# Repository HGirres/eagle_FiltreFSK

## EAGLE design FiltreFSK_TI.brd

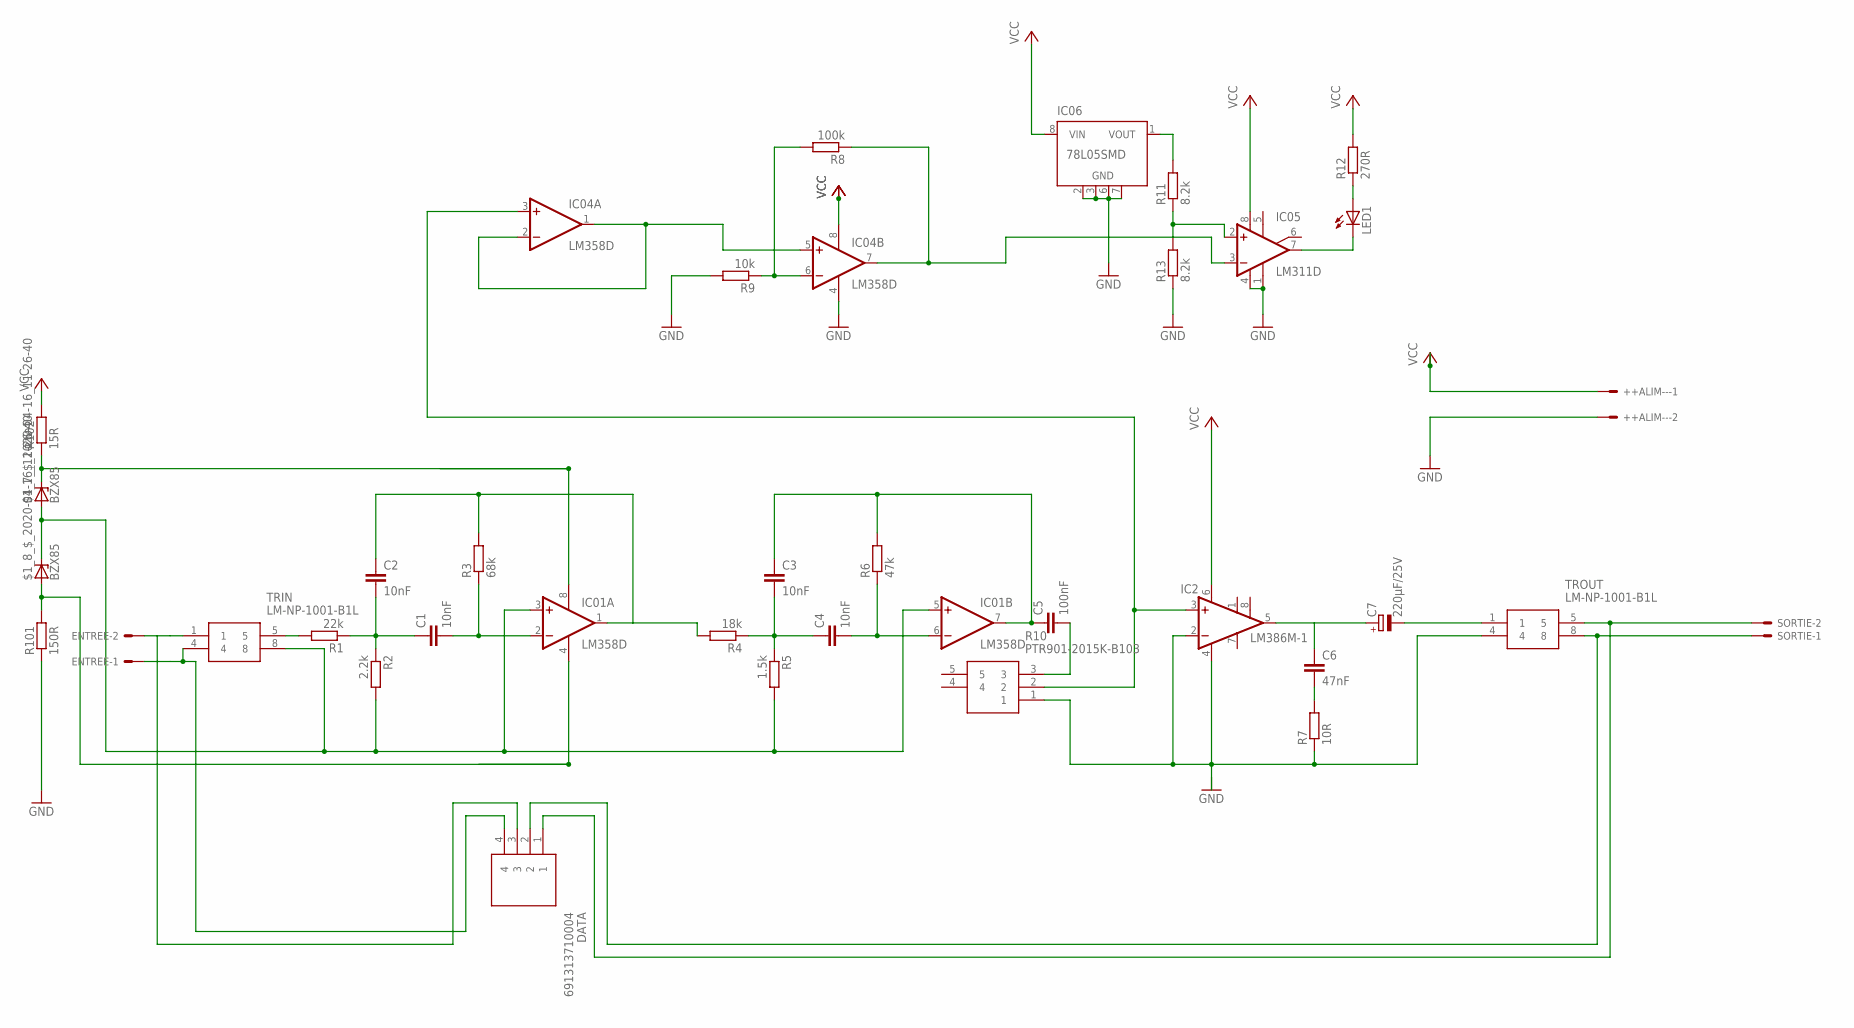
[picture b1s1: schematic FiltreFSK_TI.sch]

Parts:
$1_7_$_2020-04-16_11-26-40, $1_8_$_2020-04-16_11-26-40: BZX85; DO41Z10
++ALIM--: KK-156-2
C1, C2, C3, C4: 10nF; C1206
C5: 100nF; C1206
C6: 47nF; C1206
C7: 220µF/25V; E3,5-8
DATA: 691313710004; SHDR4W140P0X500_1X4_2200X1200X
ENTREE: KK-156-2
IC01, IC04: LM358D; SO08
IC2: LM386M-1; SO08
IC05: LM311D; SO08
IC06: 78L05SMD; SO08
LED1: LED5MM
R1: 22k; R1206
R2: 2.2k; R1206
R3: 68k; R1206
R4: 18k; R1206
R5: 1.5k; R1206
R6: 47k; R1206
R7: 10R; R1206
R8: 100k; R1206
R9: 10k; R1206
R10: PTR901-2015K-B103; PTR9012015KB103
R11, R13: 8.2k; R1210
R12: 270R; R1206
R101: 150R; 0207/10
R102: 15R; 0207/10
SORTIE: KK-156-2
TRIN: LM-NP-1001-B1L; LMNP1001B1L
TROUT: LM-NP-1001-B1L; LMNP1001B1L

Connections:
GND: ++ALIM--.2, IC2.2 (-IN), IC2.4 (GND), IC04.4 (V-), IC05.1 (GND), IC05.4 (V-), IC06.2 (GND), IC06.3 (GND), IC06.6 (GND), IC06.7 (GND), R7.1, R9.2, R10.1, R13.1, R101.1, TROUT.4
unnamed: DATA.3, ENTREE.2, TRIN.1
unnamed: $1_7_$_2020-04-16_11-26-40.A, $1_8_$_2020-04-16_11-26-40.C, IC01.3 (+IN), IC01.5 (+IN), R2.2, R5.2, TRIN.8
unnamed: $1_8_$_2020-04-16_11-26-40.A, IC01.4 (V-), R101.2
unnamed: C1.1, C2.2, R1.1, R2.1
unnamed: C2.1, IC01.1 (OUT), R3.2, R4.2
unnamed: C1.2, IC01.2 (-IN), R3.1
unnamed: DATA.4, ENTREE.1, TRIN.4
unnamed: IC2.3 (+IN), IC04.3 (+IN), R10.2
unnamed: C6.2, R7.2
unnamed: C5.2, R10.3
unnamed: DATA.2, SORTIE.1, TROUT.8
unnamed: C6.1, C7.+, IC2.5 (OUT)
unnamed: R1.2, TRIN.5
unnamed: C7.-, TROUT.1
unnamed: IC04.7 (OUT), IC05.3 (-IN), R8.1
unnamed: $1_7_$_2020-04-16_11-26-40.C, IC01.8 (V+), R102.1
unnamed: IC04.6 (-IN), R8.2, R9.1
unnamed: IC05.7 (OUT), LED1.K (C)
unnamed: LED1.A, R12.1
unnamed: IC06.1 (VOUT), R11.2
unnamed: DATA.1, SORTIE.2, TROUT.5
unnamed: IC05.2 (+IN), R11.1, R13.2
unnamed: IC04.1 (OUT), IC04.2 (-IN), IC04.5 (+IN)
unnamed: C3.2, C4.1, R4.1, R5.1
unnamed: C3.1, C5.1, IC01.7 (OUT), R6.2
unnamed: C4.2, IC01.6 (-IN), R6.1
VCC: ++ALIM--.1, IC2.6 (VS), IC04.8 (V+), IC05.8 (V+), IC06.8 (VIN), R12.2, R102.2

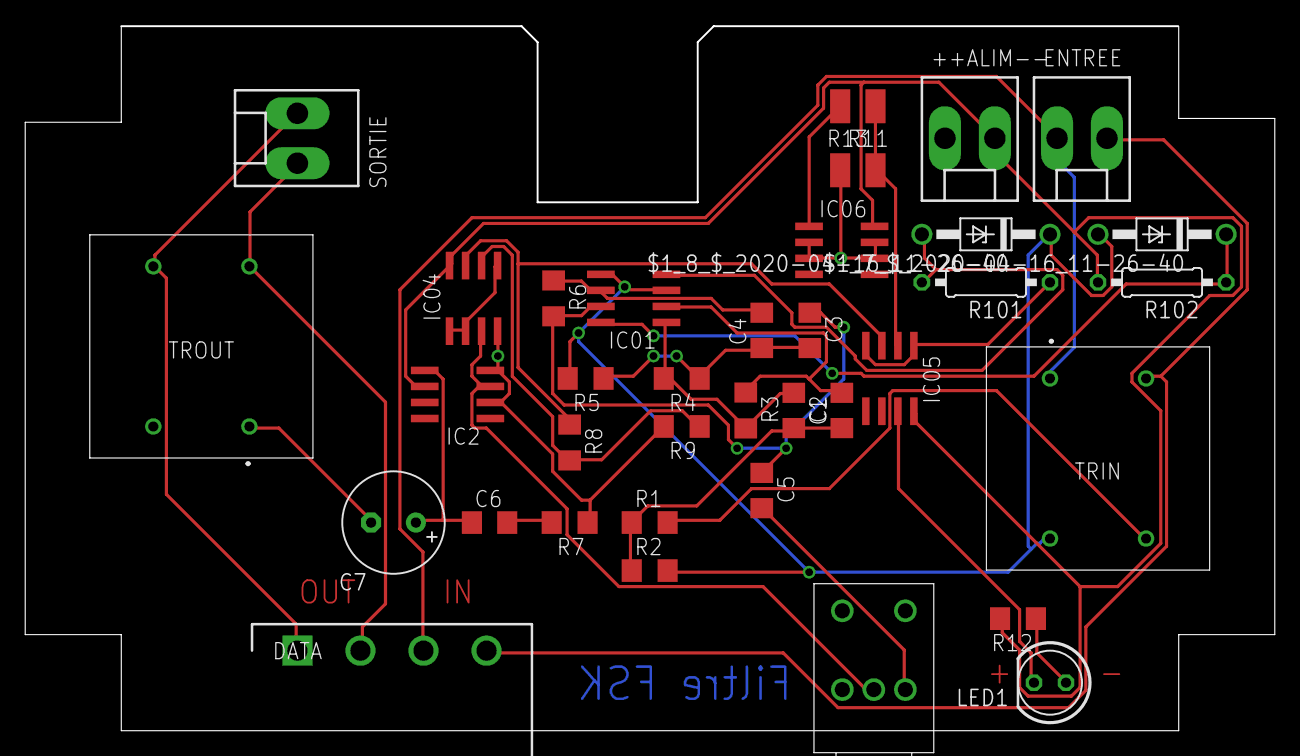
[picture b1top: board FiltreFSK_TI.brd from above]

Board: 2 copper layers, 99.0 x 55.8 mm, 36 parts (0 on the bottom side), 28 nets.

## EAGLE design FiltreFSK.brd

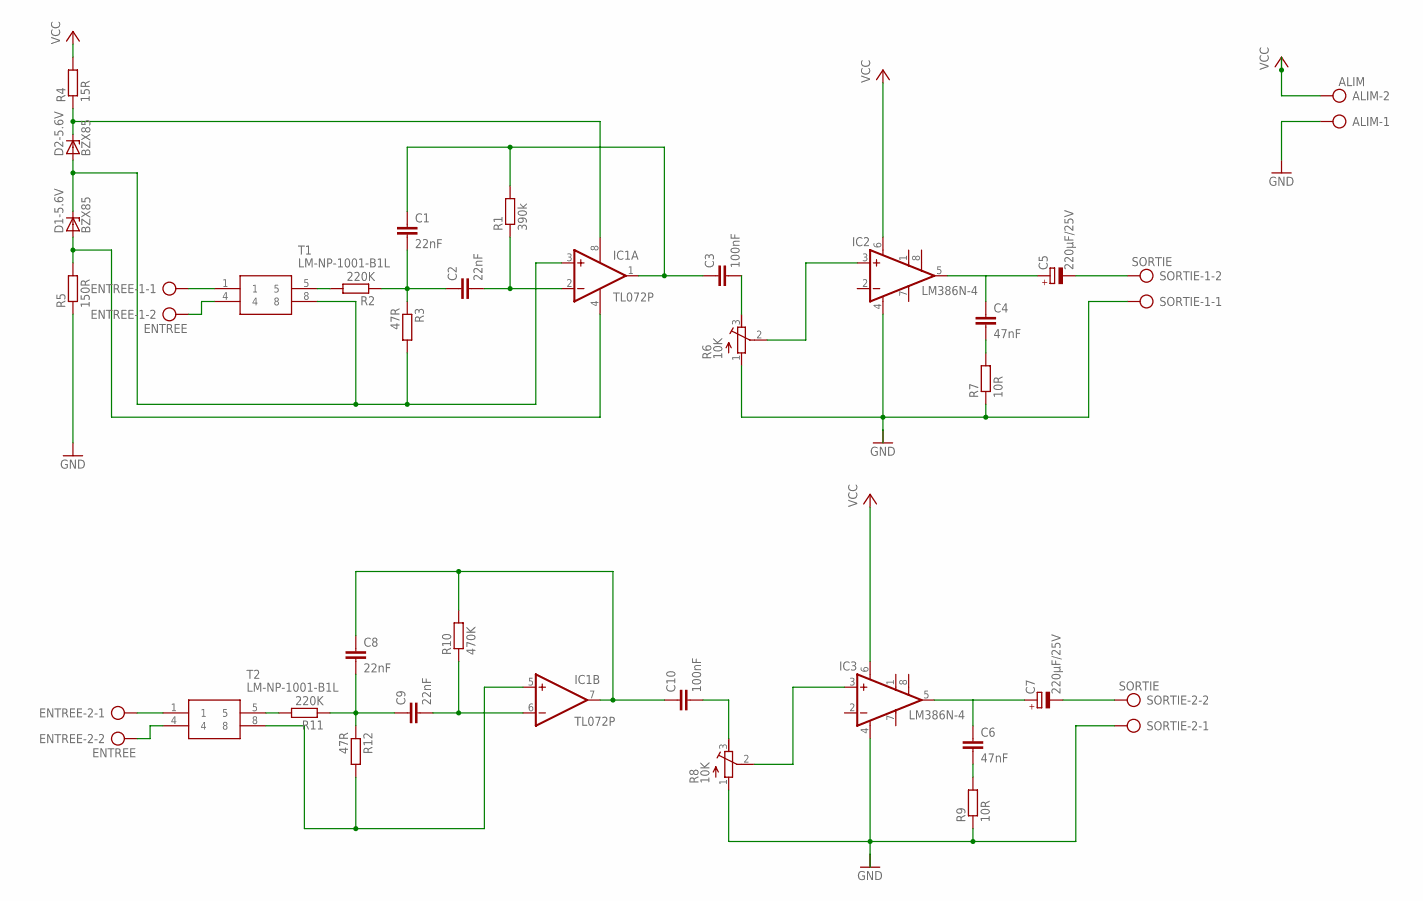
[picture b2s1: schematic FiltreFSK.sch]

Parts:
ALIM: ALIM; AK500/2-H
C1, C2, C8, C9: 22nF; C050-025X075
C3, C10: 100nF; C075-042X103
C4, C6: 47nF; C050-025X075
C5, C7: 220µF/25V; E3,5-8
D1-5.6V, D2-5.6V: BZX85; DO41Z10
ENTREE-1, ENTREE-2: ENTREE; AK500/2-H
IC1: TL072P; DIL08
IC2, IC3: LM386N-4; DIL08
R1: 390k; 0207/10
R2, R11: 220K; 0207/10
R3, R12: 47R; 0207/10
R4: 15R; 0207/10
R5: 150R; 0207/10
R6, R8: 10K; RTRIM3339P
R7, R9: 10R; 0207/10
R10: 470K; 0207/10
SORTIE-1, SORTIE-2: SORTIE; AK500/2-H
T1, T2: LM-NP-1001-B1L; LMNP1001B1L

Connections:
GND: ALIM.1, IC2.4 (GND), IC3.4 (GND), R5.1, R6.1 (A), R7.1, R8.1 (A), R9.1, SORTIE-1.1, SORTIE-2.1
unnamed: D2-5.6V.C, IC1.8 (V+), R4.1
unnamed: D1-5.6V.C, D2-5.6V.A, IC1.3 (+IN), R3.2, T1.8
unnamed: D1-5.6V.A, IC1.4 (V-), R5.2
unnamed: C1.2, C2.1, R2.1, R3.1
unnamed: C1.1, C3.1, IC1.1 (OUT), R1.2
unnamed: C2.2, IC1.2 (-IN), R1.1
unnamed: ENTREE-1.1, T1.1
unnamed: IC2.3 (+IN), R6.2 (S)
unnamed: C4.2, R7.2
unnamed: C3.2, R6.3 (E)
unnamed: ENTREE-1.2, T1.4
unnamed: C4.1, C5.+, IC2.5 (OUT)
unnamed: R2.2, T1.5
unnamed: C5.-, SORTIE-1.2
unnamed: C10.2, R8.3 (E)
unnamed: IC3.3 (+IN), R8.2 (S)
unnamed: C6.2, R9.2
unnamed: C6.1, C7.+, IC3.5 (OUT)
unnamed: C7.-, SORTIE-2.2
unnamed: IC1.5 (+IN), R12.2, T2.8
unnamed: C8.2, C9.1, R11.1, R12.1
unnamed: C8.1, C10.1, IC1.7 (OUT), R10.2
unnamed: C9.2, IC1.6 (-IN), R10.1
unnamed: ENTREE-2.1, T2.1
unnamed: ENTREE-2.2, T2.4
unnamed: R11.2, T2.5
VCC: ALIM.2, IC2.6 (VS), IC3.6 (VS), R4.2

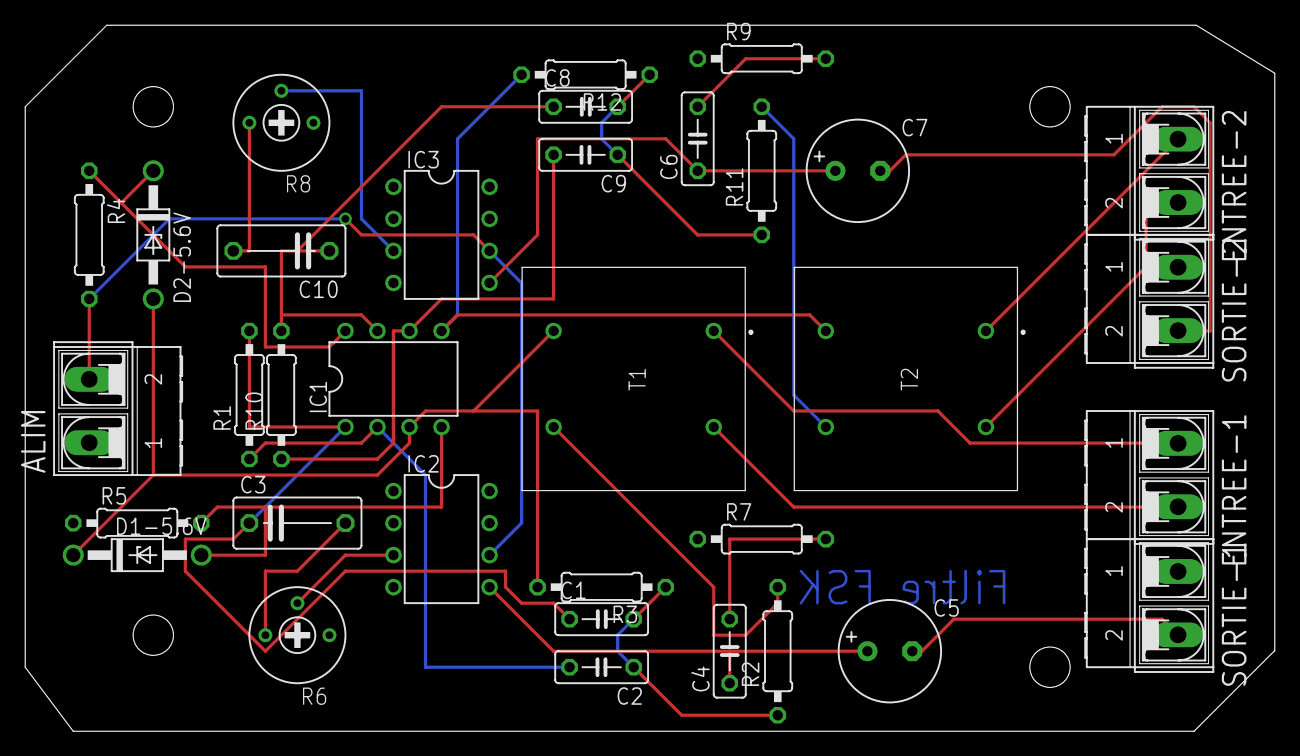
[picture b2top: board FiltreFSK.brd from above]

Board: 2 copper layers, 99.1 x 56.0 mm, 34 parts (0 on the bottom side), 28 nets.

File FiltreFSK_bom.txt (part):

Partlist exported from C:/Users/girresh/Documents/eagle/FiltreFSK/FiltreFSK.sch at 26/11/2019 09:10:11

Part Value          Device          Package      Description                                                    ALLIED_NUMBER ALLIED_PRICE-STOCK                                         DESCRIPTION                                                    HEIGHT MANUFACTURER_NAME MANUFACTURER_PART_NUMBER MF MOUSER_PART_NUMBER MOUSER_PRICE-STOCK                                                   MPN OC_FARNELL OC_NEWARK RS_PART_NUMBER RS_PRICE-STOCK                                
C1   22nF           C-EU050-025X075 C050-025X075 CAPACITOR, European symbol                                                                                                                                                                                                                                                                                                                                                                                                                
C2   22nF           C-EU050-025X075 C050-025X075 CAPACITOR, European symbol                                                                                                                                                                                                                                                                                                                                                                                                                
C3   100nF          C-EU075-042X103 C075-042X103 CAPACITOR, European symbol                                                                                                                                                                                                                                                                                                                                                                                                                
C4   47nF           C-EU050-025X075 C050-025X075 CAPACITOR, European symbol                                                                                                                                                                                                                                                                                                                                                                                                                
C5   220µF/25V      CPOL-EUE3.5-8   E3,5-8       POLARIZED CAPACITOR, European symbol                                                                                                                                                                                                                                                                                                                                                                                                      
C6   47nF           C-EU050-025X075 C050-025X075 CAPACITOR, European symbol                                                                                                                                                                                                                                                                                                                                                                                                                
C7   220µF/25V      CPOL-EUE3.5-8   E3,5-8       POLARIZED CAPACITOR, European symbol                                                                                                                                                                                                                                                                                                                                                                                                      
C8   22nF           C-EU050-025X075 C050-025X075 CAPACITOR, European symbol                                                                                                                                                                                                                                                                                                                                                                                                                
C9   22nF           C-EU050-025X075 C050-025X075 CAPACITOR, European symbol                                                                                                                                                                                                                                                                                                                                                                                                                
C10  100nF          C-EU075-042X103 C075-042X103 CAPACITOR, European symbol                                                                                                                                                                                                                                                                                                                                                                                                                
D1   BZX85          BZX85           DO41Z10      Z DIODE                                                                                                                                                                                                                                                                                                                                                                                                                                   
D2   BZX85          BZX85           DO41Z10      Z DIODE                                                                                                                                                                                                                                                                                                                                                                                                                                   
IC1  TL072P         TL072P          DIL08        OP AMP                                                                                                                                                                                                                                                                                                                                                                                                                                    
IC2  LM386N-4       LM386N-4        DIL08        Low Voltage Audio Power Amplifier                                                                                                                                                                                                                                                                                                                                                                                                         
IC3  LM386N-4       LM386N-4        DIL08        Low Voltage Audio Power Amplifier                                                                                                                                                                                                                                                                                                                                                                                                         
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
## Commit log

2023-03-07 Version initiale deu filtre/ampli FSK
2023-03-07 Version nettoyeée (pour de vrai, avec git rm)
